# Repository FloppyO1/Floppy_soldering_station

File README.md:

## Floppy Soldering Station v3.0
The Floppy soldering station 3.0 is a DIY soldering station, easy to make and inexpensive. It is great for learning and having a good workshop tool at the same time.

https://youtu.be/hezzL1TSIhk

## Support this project with a donation

To support this project you can make a donation via PayPal or buy a Floppy Board:

https://www.paypal.com/paypalme/floppylab

https://ko-fi.com/floppylab

## License

[CERN Open Hardware Licence Version 2 - Strongly Reciprocal](https://choosealicense.com/licenses/cern-ohl-s-2.0/#)

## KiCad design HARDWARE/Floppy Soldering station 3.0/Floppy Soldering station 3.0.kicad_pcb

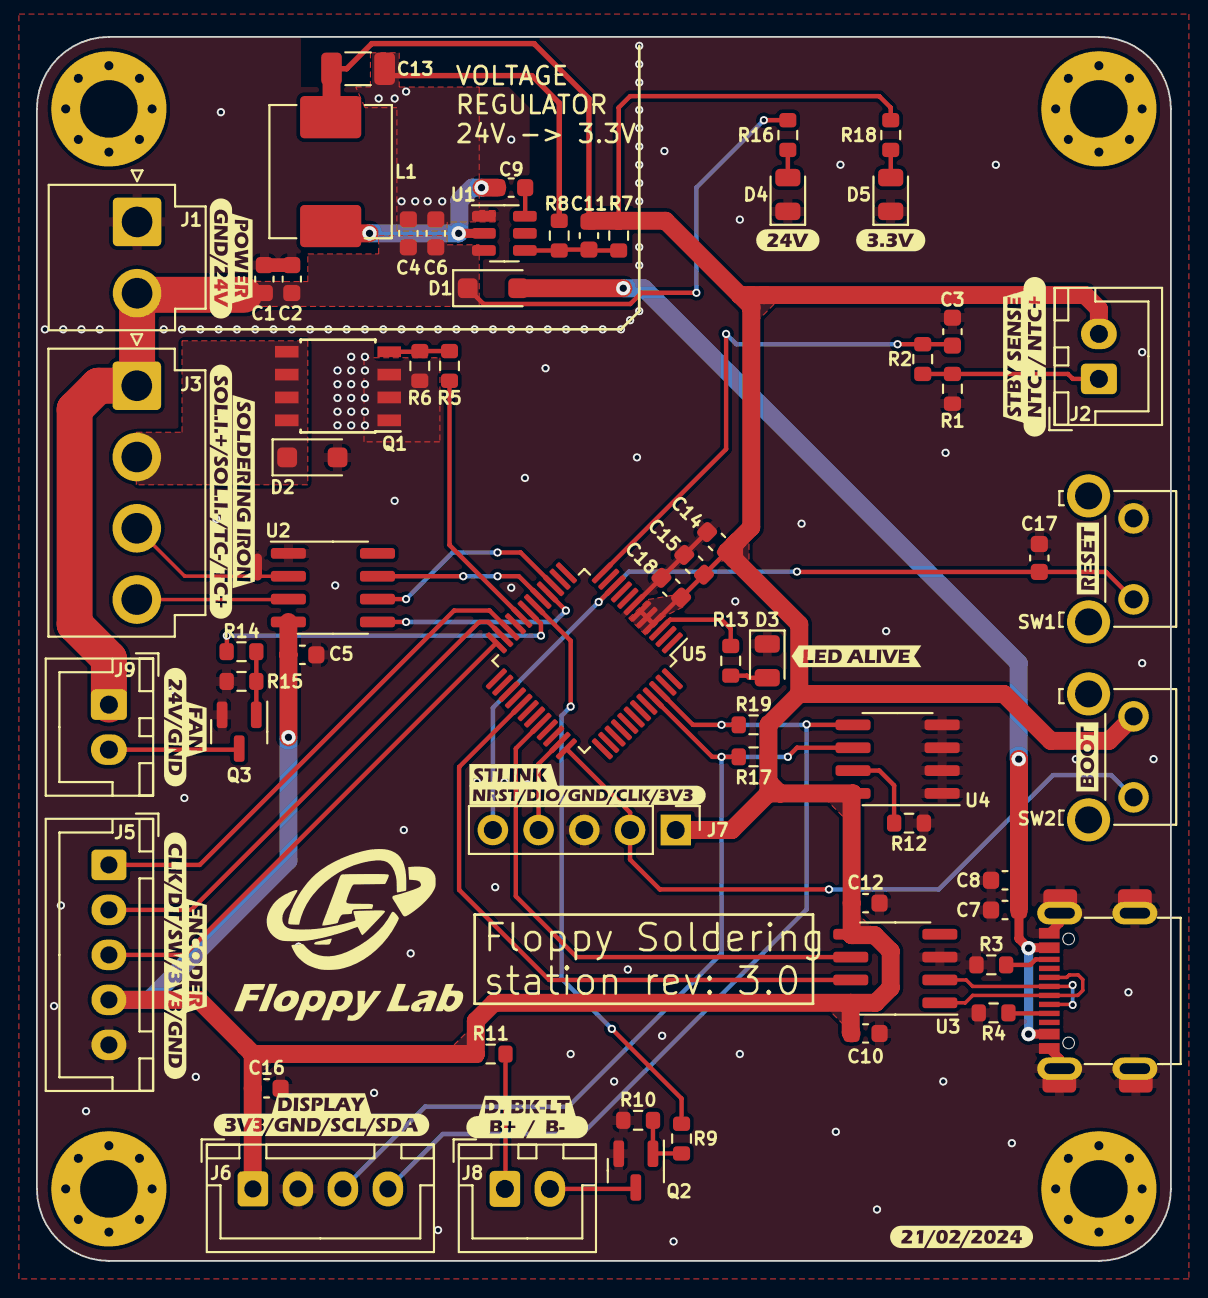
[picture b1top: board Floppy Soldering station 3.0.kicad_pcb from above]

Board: 2 copper layers, 63.0 x 68.0 mm, 89 parts (0 on the bottom side), 43 nets.

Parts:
C1, C4, C7: 10u; C_0603_1608Metric
C2, C5, C6, C8, C9, C10, C12, C15, C16, C17, C18: 100n; C_0603_1608Metric
C3, C14: 4.7u; C_0603_1608Metric
C11: 56p; C_0603_1608Metric
C13: 47u; C_1206_3216Metric
D1, D2: SM4007PL; D_SOD-123F
D3: LED_ALIVE; LED_0805_2012Metric
D4: 24V; LED_0805_2012Metric
D5: 3V3; LED_0805_2012Metric
H1, H2, H3, H4: MountingHole; MountingHole_3.2mm_M3_Pad_Via
J1: 24V; JST_VH_B2P-VH-B_1x02_P3.96mm_Vertical
J2: NTC STBY; JST_XH_B2B-XH-A_1x02_P2.50mm_Vertical
J3: STILO; JST_VH_B4P-VH-B_1x04_P3.96mm_Vertical
J4: USB-C_304A-ACP16X; USB_C_304A-ACP16X
J5: ENCODER; JST_XH_B5B-XH-A_1x05_P2.50mm_Vertical
J6: DISPLAY; JST_XH_B4B-XH-A_1x04_P2.50mm_Vertical
J7: ST-LINK; PinHeader_1x05_P2.54mm_Vertical
J8: DISPLAY BUCKLIGHT; JST_XH_B2B-XH-A_1x02_P2.50mm_Vertical
J9: FAN; JST_XH_B2B-XH-A_1x02_P2.50mm_Vertical
L1: FXL0630-100-M; L_Abracon_ASPI-0630LR
NT1: T/C- to GND; NetTie-2_SMD_Pad0.5mm
Q1: BSO110N03MSG; PG-DSO-8
Q2, Q3: AO3400A; SOT-23
R1, R2, R9, R13, R14, R16, R18: 1k; R_0603_1608Metric
R3, R4, R17, R19: 5.1k; R_0603_1608Metric
R5: 510; R_0603_1608Metric
R6, R7, R10, R15: 100k; R_0603_1608Metric
R8: 22.1k; R_0603_1608Metric
R11: 100; R_0603_1608Metric
R12: 10k; R_0603_1608Metric
SW1: RESET; SW_SPST_Omron_B3F-315x_Angled
SW2: BOOT0; SW_SPST_Omron_B3F-315x_Angled
U1: TPS54202DDC; SOT-23-6
U2: MAX6675; SOIC-8_3.9x4.9mm_P1.27mm
U3: CH340N; SOIC-8_3.9x4.9mm_P1.27mm
U4: AT24C32; SOIC-8_3.9x4.9mm_P1.27mm
U5: STM32G070CBTx; LQFP-48_7x7mm_P0.5mm
kibuzzard-65D5CE26: G***; kibuzzard-65D5CE26
kibuzzard-65D5CEBD: G***; kibuzzard-65D5CEBD
kibuzzard-65D5D1B7: G***; kibuzzard-65D5D1B7
kibuzzard-65D5D1D2: G***; kibuzzard-65D5D1D2
kibuzzard-65D5D3BD: G***; kibuzzard-65D5D3BD
kibuzzard-65D5D3CA: G***; kibuzzard-65D5D3CA
kibuzzard-65D5D4B6: G***; kibuzzard-65D5D4B6
kibuzzard-65D5D4FE: G***; kibuzzard-65D5D4FE
kibuzzard-65D5D5E6: G***; kibuzzard-65D5D5E6
kibuzzard-65D5D7D5: G***; kibuzzard-65D5D7D5
kibuzzard-65D5D7E7: G***; kibuzzard-65D5D7E7
kibuzzard-65D5D32E: G***; kibuzzard-65D5D32E
kibuzzard-65D5D52E: G***; kibuzzard-65D5D52E
kibuzzard-65D5D69C: G***; kibuzzard-65D5D69C
kibuzzard-65D5D154: G***; kibuzzard-65D5D154
kibuzzard-65D5D342: G***; kibuzzard-65D5D342
kibuzzard-65D5D366: G***; kibuzzard-65D5D366
kibuzzard-65D5D519: G***; kibuzzard-65D5D519
kibuzzard-65D5D545: G***; kibuzzard-65D5D545
kibuzzard-65D5D557: G***; kibuzzard-65D5D557
kibuzzard-65D5D985: G***; kibuzzard-65D5D985
kibuzzard-65D705D3: G***; kibuzzard-65D705D3

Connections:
+3V3: C5.2, C10.1, C11.2, C12.1, C13.1, C14.1, C15.1, C16.1, C18.2, J2.2, J5.4, J6.1, J7.1, L1.2, R7.2, R11.2, R17.2, R18.1, R19.1, SW2.1, U2.4 (Vcc), U3.5 (VCC), U3.8 (V3), U4.8 (VCC), U5.4 (VBAT), U5.5 (VREF+), U5.6 (VDD)
+24V: C1.1, C2.1, C4.1, C6.1, D1.1 (K), J1.2, J3.1, J9.1, R16.1, U1.3 (VIN)
/BUCKLIGHT_PWM: R9.2, U5.18 (PA7)
/BUCK_BOOT: C9.2, U1.6 (BOOT)
/BUCK_FBK: C11.1, R7.1, R8.2, U1.4 (FB)
/BUCK_SW: C9.1, L1.1, U1.2 (SW)
/D+: J4.6 (DP1), J4.8 (DP2), U3.1 (UD+)
/D-: J4.5 (DN2), J4.7 (DN1), U3.2 (UD-)
/ENCODER_CLK: J5.1, U5.22 (PB10)
/ENCODER_DT: J5.2, U5.23 (PB11)
/ENCODER_SW: J5.3, U5.24 (PB12)
/FAN_PWM: R14.2, U5.19 (PB0)
/I2C1_SCL: J6.3, R17.1, U4.6 (SCL), U5.45 (PB6)
/I2C1_SDA: J6.4, R19.2, U4.5 (SDA), U5.46 (PB7)
/MCU_RX: U3.6 (TXD), U5.32 (PA10/NC)
/MCU_TX: U3.7 (RXD), U5.29 (PA9/NC)
/NRST: C17.1, J7.5, SW1.2, U5.10 (NRST)
/PA13/SWDIO: J7.4, U5.35 (PA13)
/PA14/SWCLK/BOOT0: J7.2, SW2.2, U5.36 (PA14)
/STBY_NTC: C3.1, R2.2, U5.12 (PA1)
/STILO+: D2.1 (K), J3.2, Q1.3 (D)
/STILO_PWM: R5.1, U5.20 (PB1)
/STILO_TEMP_CSN: U2.6 (CS), U5.15 (PA4)
/STILO_TEMP_MISO: U2.7 (SO), U5.17 (PA6)
/STILO_TEMP_SCK: U2.5 (SCK), U5.16 (PA5)
/T/C+: J3.4, U2.3 (T+)
/T/C-: J3.3, NT1.2, U2.2 (T-)
/WP: R12.1, U4.7 (WP)
GND: C1.2, C2.2, C3.2, C4.2, C5.1, C6.2, C7.2, C8.2, C10.2, C12.2, C13.2, C14.2, C15.2, C16.2, C17.2, C18.1, D2.2 (A), D3.1 (K), D4.1 (K), D5.1 (K), J1.1, J4.1 (GND_1), J4.12 (GND_2), J4.13 (SHIELD), J5.5, J6.2, J7.3, NT1.1, Q1.1 (S), Q2.2 (S), Q3.2 (S), R1.2, R3.1, R4.2, R6.2, R8.1, R10.2, R12.2, R15.2, SW1.1, U1.1 (GND), U2.1 (GND), U3.3 (GND), U4.1 (A0), U4.2 (A1), U4.3 (A2), U4.4 (GND), U5.7 (VSS)
unnamed: D3.2 (A), R13.2
unnamed: D4.2 (A), R16.2
unnamed: D5.2 (A), R18.2
unnamed: J2.1, R1.1, R2.1
unnamed: J4.4 (CC1), R4.1
unnamed: J4.10 (CC2), R3.2
unnamed: J8.1, R11.1
unnamed: J8.2, Q2.3 (D)
unnamed: J9.2, Q3.3 (D)
unnamed: Q1.2 (G), R5.2, R6.1
unnamed: Q2.1 (G), R9.1, R10.1
unnamed: Q3.1 (G), R14.1, R15.1
unnamed: R13.1, U5.3 (PC15)
VBUS: C7.1, C8.1, D1.2 (A), J4.2 (VBUS), J4.11 (VBUS)

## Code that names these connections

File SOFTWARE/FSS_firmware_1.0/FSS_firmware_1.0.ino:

/*
This code was written by Floppy Lab for the Floppy Soldering Station 3.0
This code is under license (check it on the github folder)
https://github.com/FloppyO1/Floppy_soldering_station.git
*/

#include <U8g2lib.h>
#include <Wire.h>
#include <max6675.h>
#include <SparkFun_External_EEPROM.h>
#include <PID_v1.h>
#include <OneButton.h>
//#include "FSS_function_definitions.h"

#define DEBUG 1

#if DEBUG == 1
#define Debug(x) Serial.print(x)
#define Debugln(x) Serial.println(x)
#else
#define Debug(x)
#define Debugln(x)
#endif

/* PINS */
// DISPLAY
#define SDA PB7            // I2C
#define SCL PB6            // I2C
#define PWM_BUCKLIGHT PA7  // PWM OUTPUT
// STBY NTC
#define NTC_STBY PA1  // ADC
// T/C
#define TC_CS PA4   // SPI
#define TC_DO PA6   // SPI
#define TC_CLK PA5  // SPI
// UART
#define UART_TX PA9   // UART
#define UART_RX PA10  // UART
// FAN
#define FAN_PWM PB0  // PWM OUTPUT
// HEATER
#define HEATER_PWM PB1  // PWM OUTPUT
// ENCODER
#define ENCODER_CLK PB10  // I/O INPUT
#define ENCODER_DT PB11   // I/O INPUT
#define ENCODER_SW PB12   // I/O INPUT
// LED
#define LED_ALIVE PC15  // I/O OUTPUT

// SETTINGS
#define ENCODER_SENSITIVITY 1  // bigger the number, smaller the sensitivity
#define FPS_DISPLAY 5
#define TC_RATE 2
#define MENU_NAME_TIME 500
#define FAN_SPEED 255

#define REAL_TEMP_FILTER 0.2

#define MAX_SETTABLE_TEMP 450
#define MIN_SETTABLE_TEMP 100
#define TEMP_SET_STEP 5

#define HEATER_PWM_FREQUENCY 10
#define AGGRESSIVE_KP 4
#define AGGRESSIVE_KI 0.2
#define AGGRESSIVE_KD 50
#define CONSERVATIVE_KP 4
#define CONSERVATIVE_KI 0.1
#define CONSERVATIVE_KD 200
#define PID_CANGE_LEVEL 100    // error at which the pid constant change to conservative

// TIPES
enum Menu {
  MENU_MAIN,
  MENU_SET_TEMP
};

enum State {
  USING,      // soldering iron in hand
  NOT_USING,  // soldering iron in holder
  STBY,       // soldering station in stby (iron in holder for lot of time)
  TC_ERR      // T/C not found
};

// GRAPHIC VARIABLES
uint8_t gif2 = 0;

// GLOBAL VARIABLES
int encoderCount = 0;
Menu menuActive = MENU_MAIN;
Menu menuPerv = MENU_MAIN;
State status = STBY;
double targetTemp = 300;
double realTemp = 0;
double solderingDuty = 0;
bool solderingEN = false;
//double realTempPrev = 0;

// T/C OBJECT
MAX6675 thermocouple(TC_CLK, TC_CS, TC_DO);
// DISPLAY OBJECT
U8G2_ST7567_ENH_DG128064I_F_HW_I2C display(U8G2_R2);  // [page buffer, size = 128 bytes]
// EXTERNAL EEPROM OBJECT
ExternalEEPROM myMem;
// PID OBJECT
double aggKp = AGGRESSIVE_KP, aggKi = AGGRESSIVE_KI, aggKd = AGGRESSIVE_KD;
double consKp = CONSERVATIVE_KP, consKi = CONSERVATIVE_KI, consKd = CONSERVATIVE_KD;
PID heaterPID(&realTemp, &solderingDuty, &targetTemp, consKp, consKi, consKd, DIRECT);
OneButton EncoderButton(ENCODER_SW, true);


void setup() {
  initSerial();
  initDisplay();
  initEncoder();
  initSolderingIron();
  initFan();

  setFanSpeed(FAN_SPEED);
  heaterPID.SetMode(AUTOMATIC);
}  // end setup


int timeDisplay = 0;
int timeTC = 0;
int timeGif = 0;
void loop() {
  	// BUTTONS
    EncoderButton.tick();


  // TERMOCOPUPLE
  if (millis() - timeTC >= 1000 / TC_RATE) {
    float temp = getTempC();
    if (!isnan(temp)) {
      realTemp = ((int)temp * REAL_TEMP_FILTER) + ((int)realTemp * (1 - REAL_TEMP_FILTER));
      //realTempPrev = realTemp;
    }
    timeTC = millis();
  }

  // GRAPHIC INTERFACE
  if (millis() - timeDisplay >= 1000 / FPS_DISPLAY) {
    //Debugln("aggiorno il display");
    changeMenu();
    switch (menuActive) {
      case MENU_MAIN:
        drawMainMenu();
        break;
      case MENU_SET_TEMP:
        drawSetTempMenu();
        break;
    }
    display.sendBuffer();  // transfer internal memory to the display
    timeDisplay = millis();
  }

  // GIFs
  if (millis() - timeGif >= 500) {
    gif2 = (gif2 + 1) % 2;
    timeGif = millis();
  }

  // SOLDERING IRON HEATER
  if (status != TC_ERR && menuActive != MENU_SET_TEMP) {
    Debugln("normal operation");
    switchOnHeater();
  } else {
    switchOffHeater();
#ifdef DEBUG
    if (status == TC_ERR) { Debugln("TC_ERR"); }
    if (menuActive == MENU_SET_TEMP) { Debugln("menu set temp"); }
#endif
  }

  if(menuActive == MENU_SET_TEMP){
    updateEncoder();
  }


  if (solderingEN) {  // soldering iron enabled set duty acording to pid
    Debugln("keeping temperature");
    keepTemp();
  } else {  // sodering iron is disabled set duty to 0
    solderingDuty = 0;
    analogWrite(0, HEATER_PWM);
  }
}  // end loop

/* ------------------------- GENERAL ------------------------- */
void initSerial() {
  Serial.setTx(UART_TX);
  Serial.setRx(UART_RX);
  Serial.begin(115200);
}

void initLed() {
  pinMode(LED_ALIVE, OUTPUT);
}

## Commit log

2024-06-17 Added all the files of the project
2024-06-17 file for printing updated
2024-06-17 Create LICENSE
